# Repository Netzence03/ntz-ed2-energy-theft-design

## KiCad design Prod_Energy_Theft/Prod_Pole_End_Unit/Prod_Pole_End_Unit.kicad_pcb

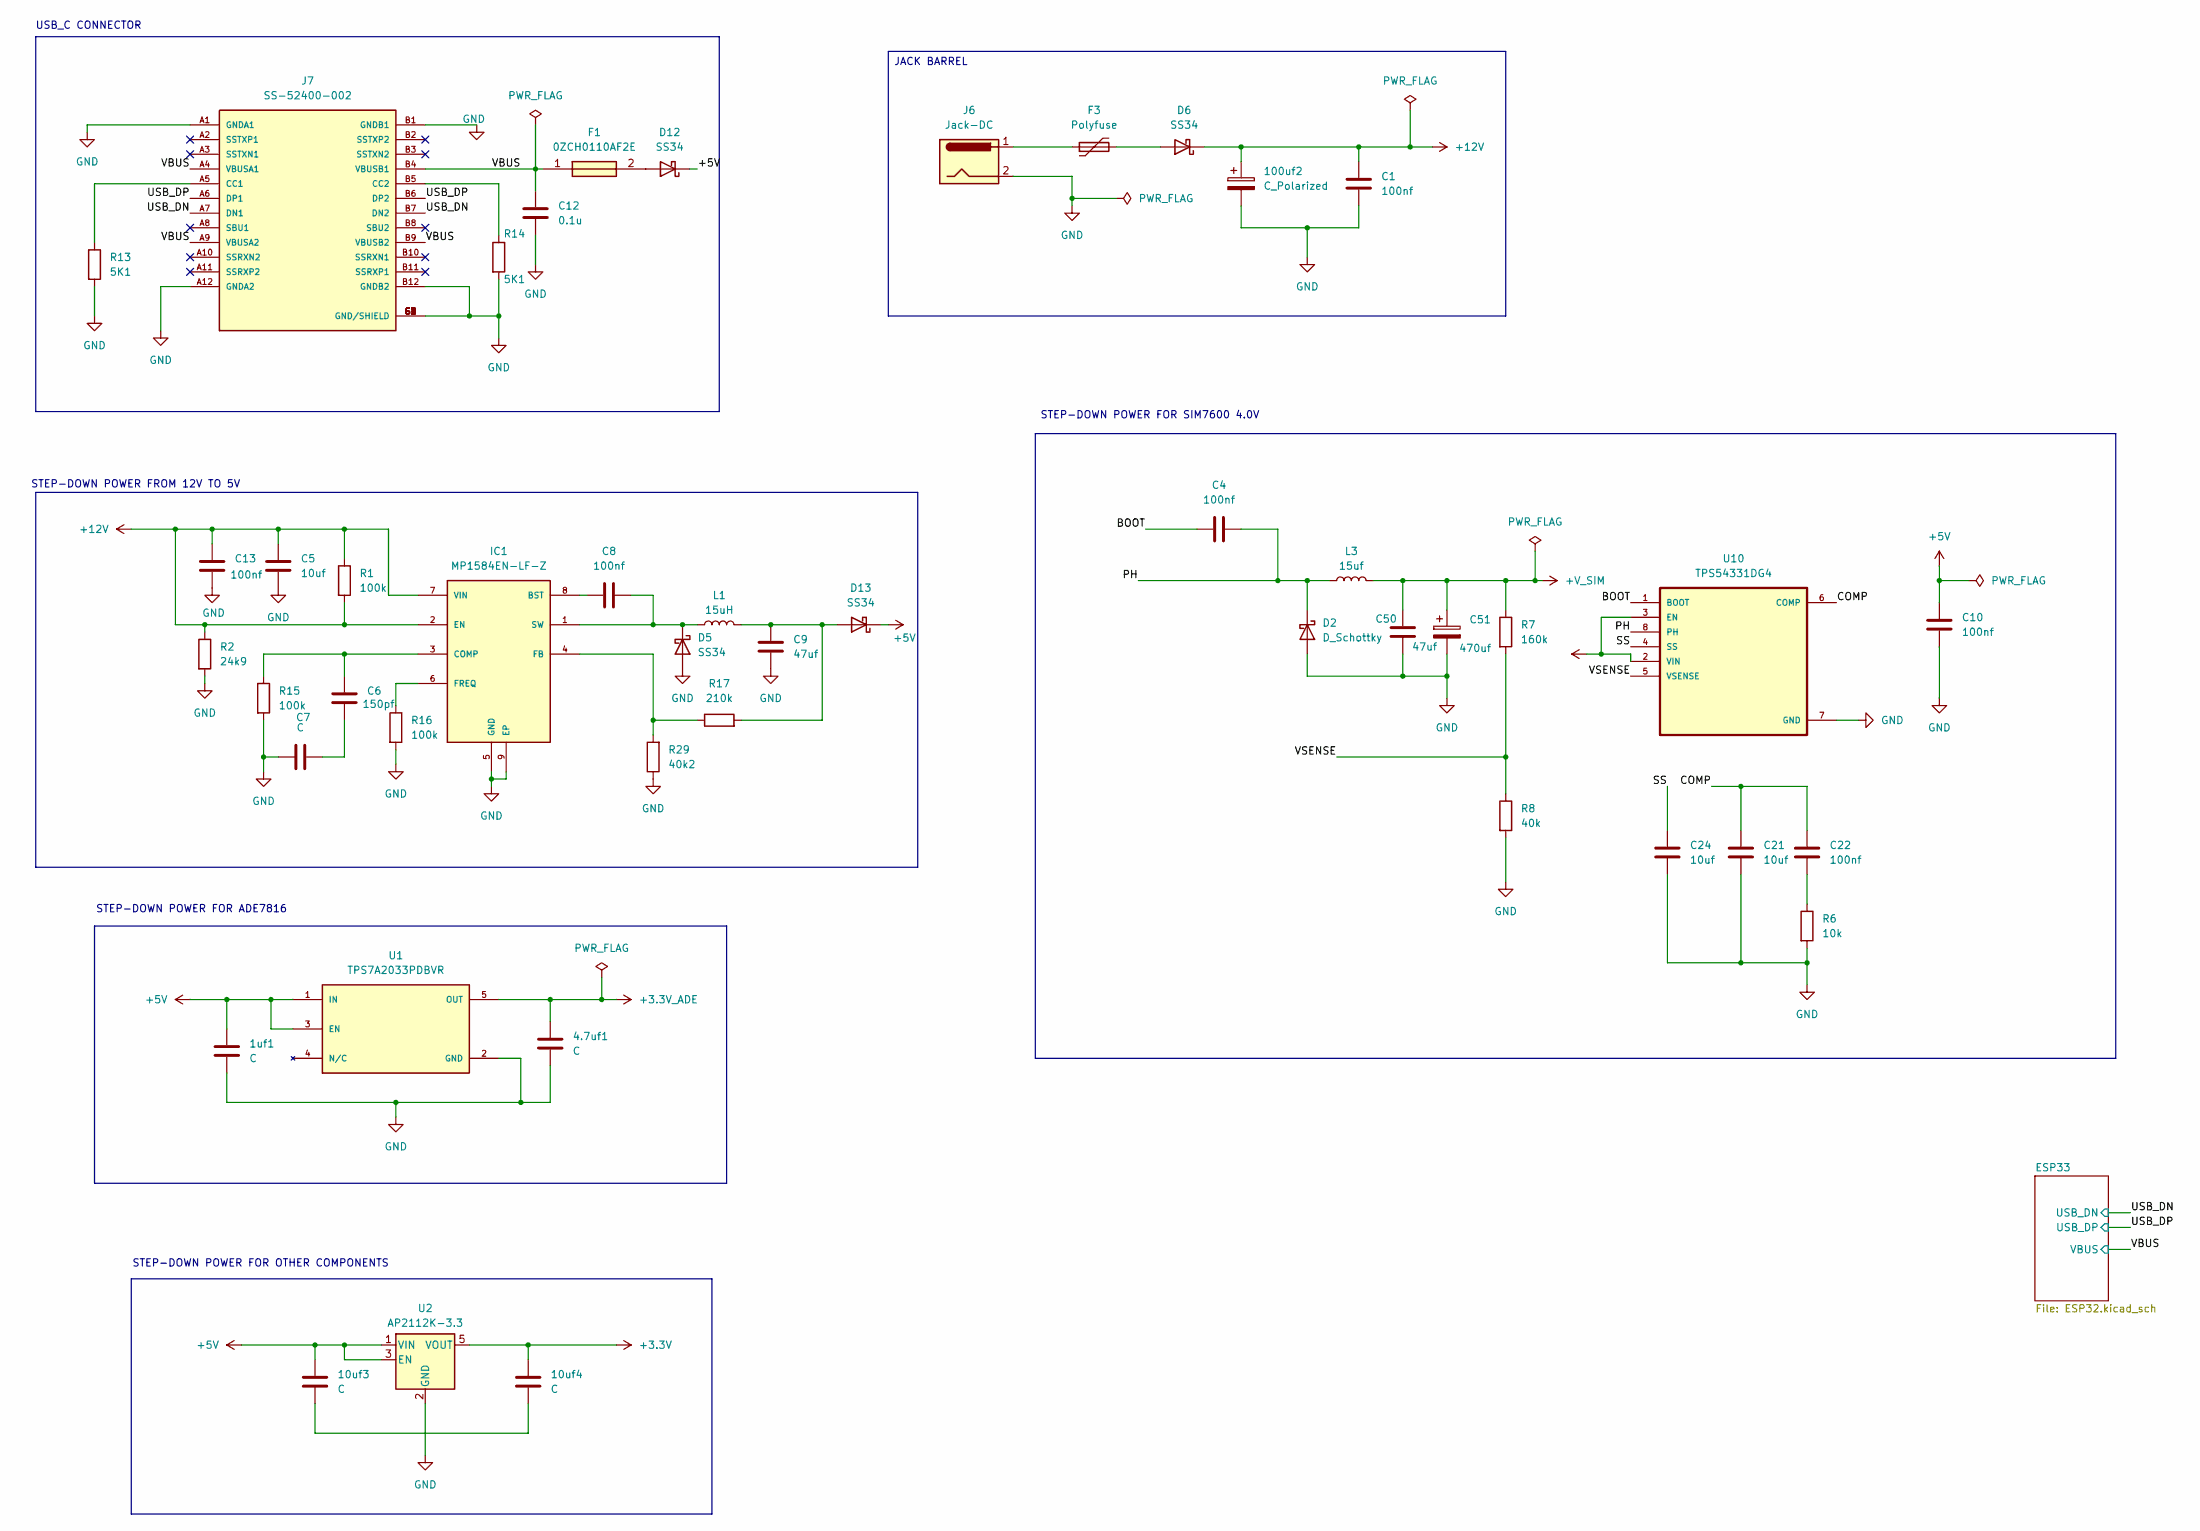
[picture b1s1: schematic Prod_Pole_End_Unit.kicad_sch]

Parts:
1uf1, 4.7uf1, 10uf3, 10uf4: C; C_0805_2012Metric
100uf2: C_Polarized; C_0805_2012Metric
C1, C4, C8, C10, C13, C22: 100nf; C_0805_2012Metric
C5, C21, C24: 10uf; C_0805_2012Metric
C6: 150pf; C_0805_2012Metric
C7: C; C_0805_2012Metric
C9: 47uf; C_0805_2012Metric; Voltage 16V; MPN GRM32ER71C476KE15
C12: 0.1u; C_0805_2012Metric
C50: 47uf; C_0805_2012Metric
C51: 470uf; C_0805_2012Metric
D2: D_Schottky; D_SMA
D5, D6, D12, D13: SS34; D_SMA
F1: 0ZCH0110AF2E; FUSC3226X100N; Manufacturer_Part_Number 0ZCH0110AF2E
F3: Polyfuse; Fuse_1206_3216Metric
IC1: MP1584EN-LF-Z; SOIC127P600X170-9N; MOUSER_PART_NUMBER 946-MP1584ENLFZ
J6: Jack-DC; BarrelJack_GCT_DCJ200-10-A_Horizontal
J7: SS-52400-002; BELFUSE_SS-52400-002; PARTREV A0
L1: 15uH; L_0805_2012Metric
L3: 15uf; L_0805_2012Metric
R1, R15, R16: 100k; R_0805_2012Metric
R2: 24k9; R_0805_2012Metric
R6: 10k; R_0805_2012Metric
R7: 160k; R_0805_2012Metric
R8: 40k; R_0805_2012Metric
R13, R14: 5K1; R_0805_2012Metric
R17: 210k; R_0805_2012Metric
R29: 40k2; R_0805_2012Metric
U1: TPS7A2033PDBVR; SOT95P280X145-5N; PARTREV H
U2: AP2112K-3.3; SOT-23-5
U10: TPS54331DG4; SOIC127P599X175-8N

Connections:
+3.3V: 10uf4.1, U2.5 (VOUT); also elsewhere on the board
+3.3V_ADE: 4.7uf1.1, U1.5 (OUT); also elsewhere on the board
+5V: 1uf1.1, 10uf3.1, C10.1, D12.1 (K), D13.1 (K), U1.1 (IN), U1.3 (EN), U2.1 (VIN), U2.3 (EN), U10.2 (VIN), U10.3 (EN)
+12V: 100uf2.1, C1.1, C5.1, C13.1, D6.1 (K), IC1.2 (EN), IC1.7 (VIN), R1.1, R1.2, R2.1
+V_SIM: C50.1, C51.1, L3.2, R7.1; also elsewhere on the board
/BOOT: C4.1, U10.1 (BOOT)
/COMP: C21.1, C22.1, U10.6 (COMP)
/PH: C4.2, D2.1 (K), L3.1, U10.8 (PH)
/SS: C24.1, U10.4 (SS)
/USB_DN: J7.A7 (DN1), J7.B7 (DN2); also elsewhere on the board
/USB_DP: J7.A6 (DP1), J7.B6 (DP2); also elsewhere on the board
/VBUS: C12.1, F1.1, J7.A4 (VBUSA1), J7.A9 (VBUSA2), J7.B4 (VBUSB1), J7.B9 (VBUSB2); also elsewhere on the board
/VSENSE: R7.2, R8.1, U10.5 (VSENSE)
GND: 1uf1.2, 4.7uf1.2, 100uf2.2, C1.2, C5.2, C7.1, C9.2, C10.2, C12.2, C13.2, C21.2, C24.2, C50.2, C51.2, D2.2 (A), D5.2 (A), IC1.5 (GND), IC1.9 (EP), J6.2, J7.A1 (GNDA1), J7.A12 (GNDA2), J7.B1 (GNDB1), J7.B12 (GNDB2), J7.G1 (GND/SHIELD), J7.G2 (GND/SHIELD), J7.G3 (GND/SHIELD), J7.G4 (GND/SHIELD), J7.S1 (GND/SHIELD), J7.S2 (GND/SHIELD), J7.S3 (GND/SHIELD), J7.S4 (GND/SHIELD), R2.2, R6.2, R8.2, R13.2, R14.2, R15.2, R16.2, R29.1, U1.2 (GND), U2.2 (GND), U10.7 (GND); also elsewhere on the board
unnamed: 10uf3.2, 10uf4.2
unnamed: C6.2, C7.2
unnamed: C22.2, R6.1
unnamed: C8.2, D5.1 (K), IC1.1 (SW), L1.1
unnamed: D6.2 (A), F3.2
unnamed: D12.2 (A), F1.2
unnamed: C9.1, D13.2 (A), L1.2, R17.2
unnamed: F3.1, J6.1
unnamed: C8.1, IC1.8 (BST)
unnamed: C6.1, IC1.3 (COMP), R15.1
unnamed: IC1.4 (FB), R17.1, R29.2
unnamed: IC1.6 (FREQ), R16.1
unnamed: J7.A5 (CC1), R13.1
unnamed: J7.B5 (CC2), R14.1

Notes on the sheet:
STEP-DOWN POWER FROM 12V TO 5V
STEP-DOWN POWER FOR ADE7816
STEP-DOWN POWER FOR SIM7600 4.0V
STEP-DOWN POWER FOR OTHER COMPONENTS
USB_C CONNECTOR
JACK BARREL

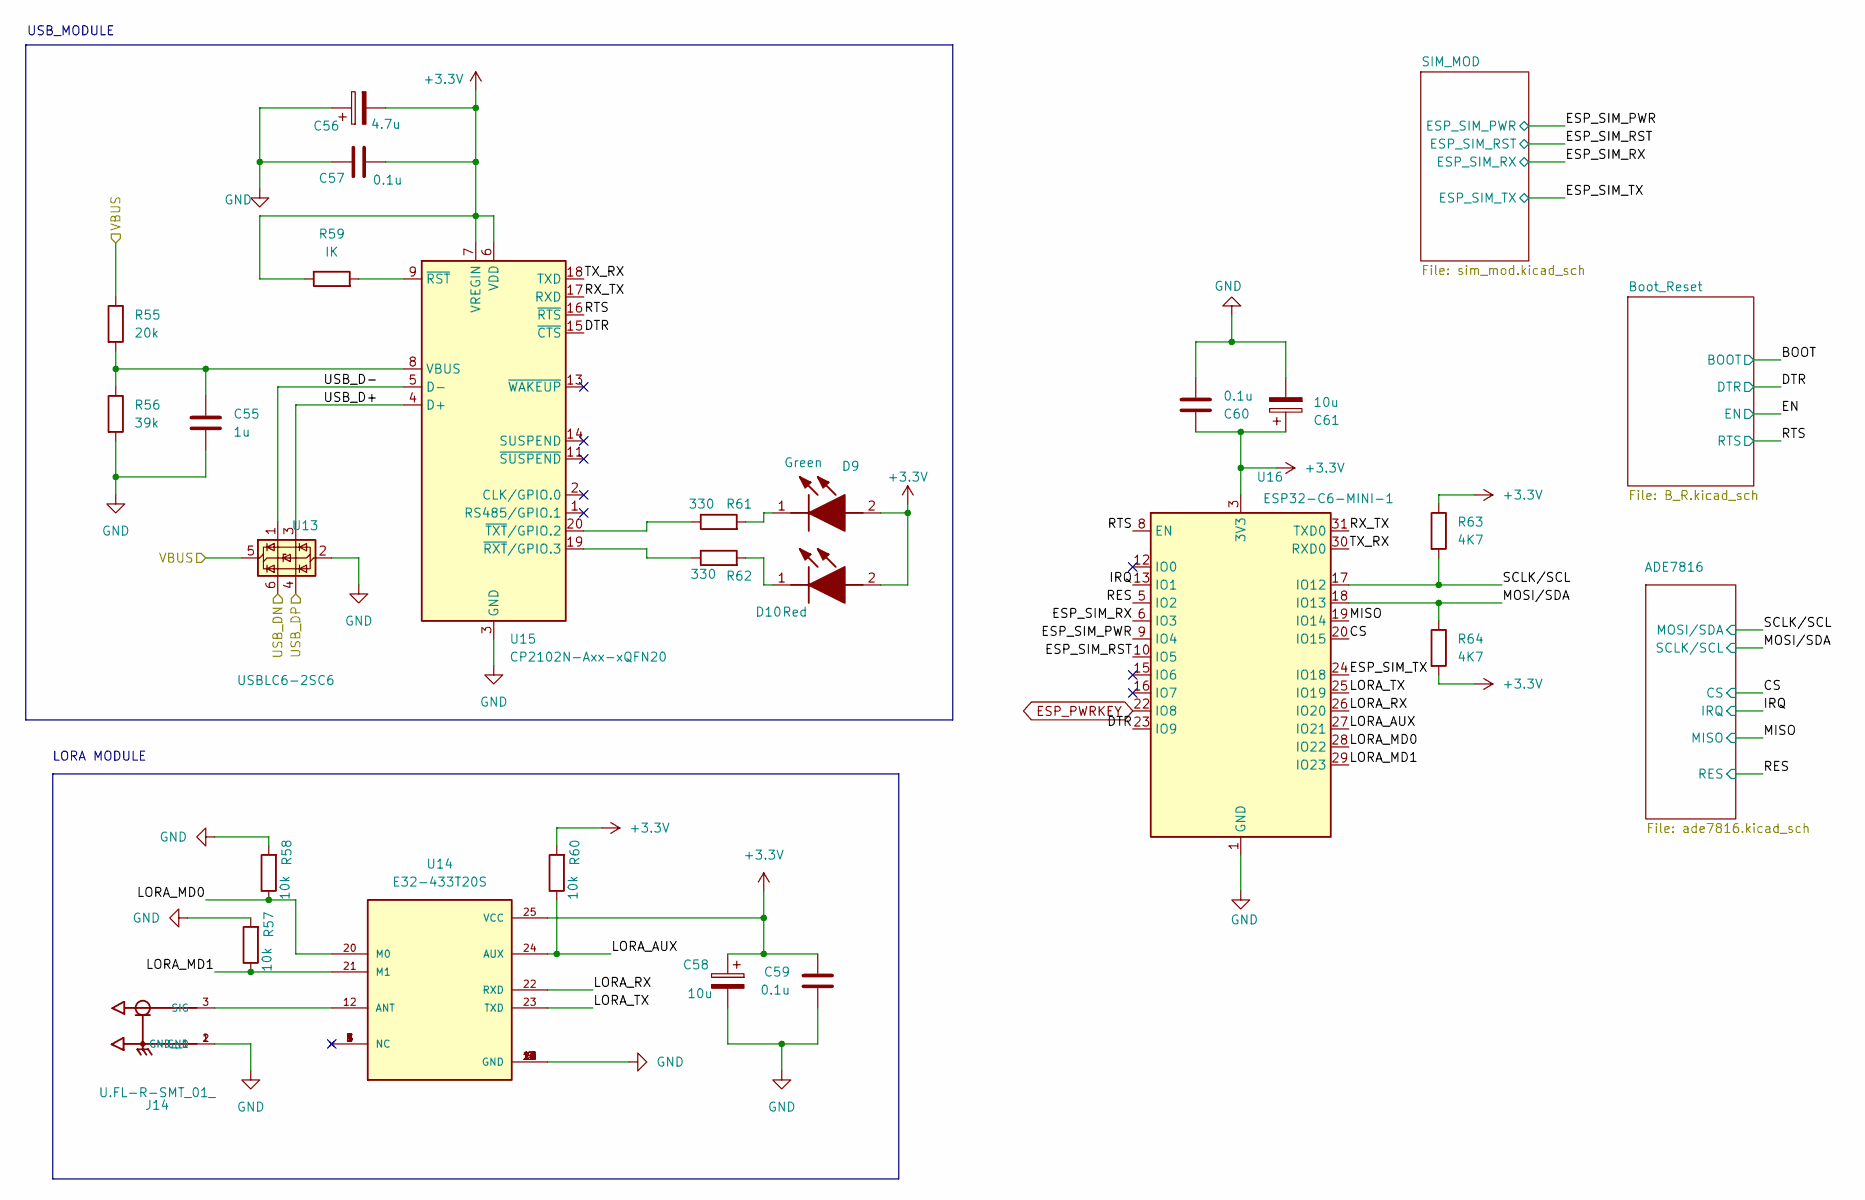
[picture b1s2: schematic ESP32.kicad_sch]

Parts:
C55: 1u; C_0805_2012Metric
C56: 4.7u; C_0805_2012Metric
C57, C59, C60: 0.1u; C_0805_2012Metric
C58, C61: 10u; C_0805_2012Metric
D9: Green; LEDC2012X120N; Manufacturer_Part_Number LTST-C170GKT; Mouser Part Number 859-LTST-C170GKT
D10: Red; LEDC2012X120N; Manufacturer_Part_Number LTST-C170KRKT; Mouser Part Number 859-LTST-C170KRKT
J14: U.FL-R-SMT_01_; HRS_U.FL-R-SMT_01_
R55: 20k; R_0805_2012Metric
R56: 39k; R_0805_2012Metric
R57, R58, R60: 10k; R_0805_2012Metric
R59: IK; R_0805_2012Metric
R61, R62: 330; R_0805_2012Metric
R63, R64: 4K7; R_0805_2012Metric
U13: USBLC6-2SC6; SOT-23-6
U14: E32-433T20S; MODULE_E32-433T20S; PARTREV 1.00
U15: CP2102N-Axx-xQFN20; IC_CP2102N-A01-GQFN20
U16: ESP32-C6-MINI-1

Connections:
+3.3V: C56.2, C57.2, C58.1, C59.1, C60.1, C61.1, D9.2 (A), D10.2 (A), R59.1, R60.2, R63.1, R64.2, U14.25 (VCC), U15.6 (VDD), U15.7 (VREGIN), U16.3 (3V3); also elsewhere on the board
/ESP33/CS: U16.20 (IO15); also elsewhere on the board
/ESP33/DTR: U15.15 (~CTS), U16.23 (IO9); also elsewhere on the board
/ESP33/ESP_SIM_PWR: U16.9 (IO4); also elsewhere on the board
/ESP33/ESP_SIM_RST: U16.10 (IO5); also elsewhere on the board
/ESP33/ESP_SIM_RX: U16.6 (IO3); also elsewhere on the board
/ESP33/ESP_SIM_TX: U16.24 (IO18); also elsewhere on the board
/ESP33/IRQ: U16.13 (IO1); also elsewhere on the board
/ESP33/LORA_AUX: R60.1, U14.24 (AUX), U16.27 (IO21)
/ESP33/LORA_MD0: R58.1, U14.20 (M0), U16.28 (IO22)
/ESP33/LORA_MD1: R57.1, U14.21 (M1), U16.29 (IO23)
/ESP33/LORA_RX: U14.22 (RXD), U16.26 (IO20)
/ESP33/LORA_TX: U14.23 (TXD), U16.25 (IO19)
/ESP33/MISO: U16.19 (IO14); also elsewhere on the board
/ESP33/MOSI/SDA: R64.1, U16.18 (IO13); also elsewhere on the board
/ESP33/RES: U16.5 (IO2); also elsewhere on the board
/ESP33/RTS: U15.16 (~RTS), U16.8 (EN); also elsewhere on the board
/ESP33/RX_TX: U15.17 (RXD), U16.31 (TXD0)
/ESP33/SCLK/SCL: R63.2, U16.17 (IO12); also elsewhere on the board
/ESP33/TX_RX: U15.18 (TXD), U16.30 (RXD0)
/ESP33/USB_D+: U13.3 (I/O2), U15.4 (D+)
/ESP33/USB_D-: U13.1 (I/O1), U15.5 (D-)
/USB_DN: U13.6 (I/O1); also elsewhere on the board
/USB_DP: U13.4 (I/O2); also elsewhere on the board
/VBUS: R55.1, U13.5 (VBUS); also elsewhere on the board
ESP_PWRKEY: U16.22 (IO8); also elsewhere on the board
GND: C55.2, C56.1, C57.1, C58.2, C59.2, C60.2, C61.2, J14.1 (GND), J14.2 (GND__1), R56.2, R57.2, R58.2, U13.2 (GND), U14.2 (GND), U14.8 (GND), U14.11 (GND), U14.13 (GND), U14.14 (GND), U14.15 (GND), U14.16 (GND), U14.19 (GND), U14.26 (GND), U15.3 (GND), U15.12 (GND), U15.21 (GND), U16.1 (GND), U16.2 (GND), U16.11 (GND), U16.14 (GND), U16.36 (GND), U16.37 (GND), U16.38 (GND), U16.39 (GND), U16.40 (GND), U16.41 (GND), U16.42 (GND), U16.43 (GND), U16.44 (GND), U16.45 (GND), U16.46 (GND), U16.47 (GND), U16.48 (GND), U16.49 (GND), U16.50 (GND), U16.51 (GND), U16.52 (GND), U16.53 (GND); also elsewhere on the board
unnamed: D9.1 (K), R61.2
unnamed: D10.1 (K), R62.2
unnamed: J14.3 (SIG), U14.12 (ANT)
unnamed: C55.1, R55.2, R56.1, U15.8 (VBUS)
unnamed: R59.2, U15.9 (~RST)
unnamed: R62.1, U15.19 (~RXT/GPIO.3)
unnamed: R61.1, U15.20 (~TXT/GPIO.2)

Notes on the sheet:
LORA MODULE
USB_MODULE

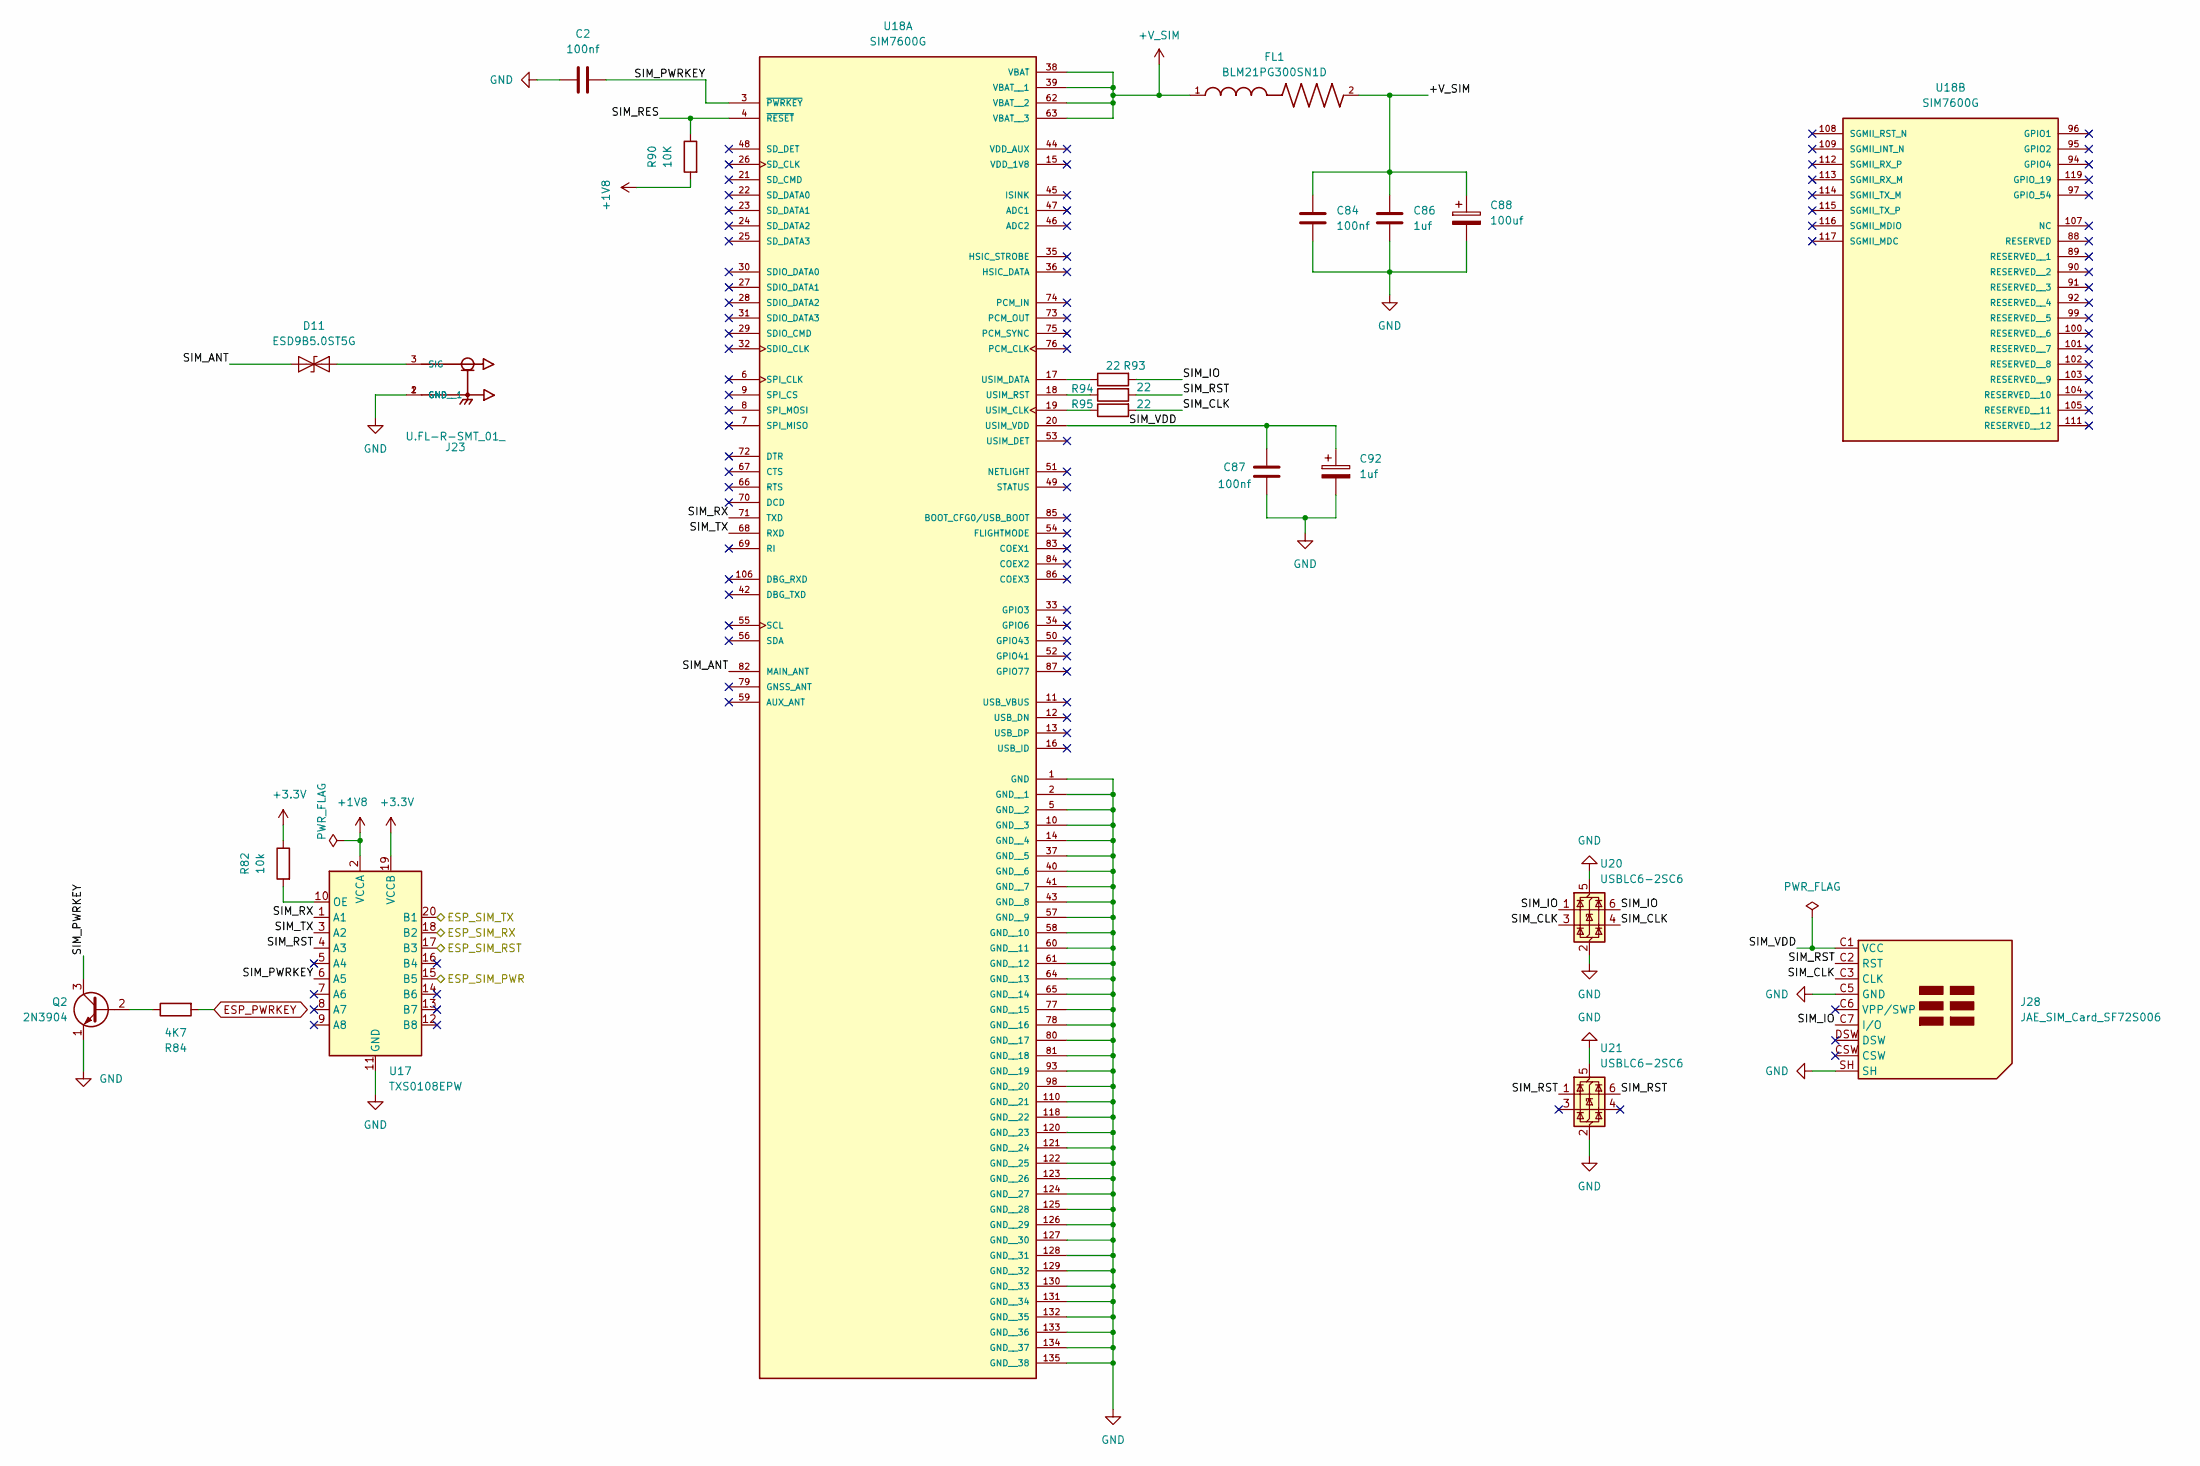
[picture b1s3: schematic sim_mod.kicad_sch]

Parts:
C2, C84, C87: 100nf; C_0805_2012Metric
C86, C92: 1uf; C_0805_2012Metric
C88: 100uf; C_0805_2012Metric
D11: ESD9B5.0ST5G; D_SOD-923
FL1: BLM21PG300SN1D; BEADC2012X105N
J23: U.FL-R-SMT_01_; HRS_U.FL-R-SMT_01_
J28: JAE_SIM_Card_SF72S006
Q2: 2N3904; TO-92_Inline
R82: 10k; R_0805_2012Metric
R84: 4K7; R_0805_2012Metric
R90: 10K; R_0805_2012Metric
R93, R94, R95: 22; R_0805_2012Metric
U17: TXS0108EPW; TSSOP-20_4.4x6.5mm_P0.65mm
U18: SIM7600G; IC_SIM7600G
U20, U21: USBLC6-2SC6; SOT-23-6

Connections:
+1V8: R90.2, U17.2 (VCCA)
+3.3V: R82.1, U17.19 (VCCB); also elsewhere on the board
+V_SIM: C84.1, C86.1, C88.1, FL1.1, FL1.2, U18.38 (VBAT), U18.39 (VBAT__1), U18.62 (VBAT__2), U18.63 (VBAT__3); also elsewhere on the board
/ESP33/ESP_SIM_PWR: U17.15 (B5); also elsewhere on the board
/ESP33/ESP_SIM_RST: U17.17 (B3); also elsewhere on the board
/ESP33/ESP_SIM_RX: U17.18 (B2); also elsewhere on the board
/ESP33/ESP_SIM_TX: U17.20 (B1); also elsewhere on the board
/ESP33/SIM_MOD/SIM_ANT: D11.1 (A1), U18.82 (MAIN_ANT)
/ESP33/SIM_MOD/SIM_CLK: J28.C3 (CLK), R95.2, U20.3 (I/O2), U20.4 (I/O2)
/ESP33/SIM_MOD/SIM_IO: J28.C7 (I/O), R93.2, U20.1 (I/O1), U20.6 (I/O1)
/ESP33/SIM_MOD/SIM_PWRKEY: C2.2, Q2.3 (C), U17.6 (A5), U18.3 (~PWRKEY)
/ESP33/SIM_MOD/SIM_RES: R90.1, U18.4 (~RESET)
/ESP33/SIM_MOD/SIM_RST: J28.C2 (RST), R94.2, U17.4 (A3), U21.1 (I/O1), U21.6 (I/O1)
/ESP33/SIM_MOD/SIM_RX: U17.1 (A1), U18.71 (TXD)
/ESP33/SIM_MOD/SIM_TX: U17.3 (A2), U18.68 (RXD)
/ESP33/SIM_MOD/SIM_VDD: C87.1, C92.1, J28.C1 (VCC), U18.20 (USIM_VDD)
ESP_PWRKEY: R84.2; also elsewhere on the board
GND: C2.1, C84.2, C86.2, C87.2, C88.2, C92.2, J23.1 (GND), J23.2 (GND__1), J28.C5 (GND), J28.SH, Q2.1 (E), U17.11 (GND), U18.1 (GND), U18.2 (GND__1), U18.5 (GND__2), U18.10 (GND__3), U18.14 (GND__4), U18.37 (GND__5), U18.40 (GND__6), U18.41 (GND__7), U18.43 (GND__8), U18.57 (GND__9), U18.58 (GND__10), U18.60 (GND__11), U18.61 (GND__12), U18.64 (GND__13), U18.65 (GND__14), U18.77 (GND__15), U18.78 (GND__16), U18.80 (GND__17), U18.81 (GND__18), U18.93 (GND__19), U18.98 (GND__20), U18.110 (GND__21), U18.118 (GND__22), U18.120 (GND__23), U18.121 (GND__24), U18.122 (GND__25), U18.123 (GND__26), U18.124 (GND__27), U18.125 (GND__28), U18.126 (GND__29), U18.127 (GND__30), U18.128 (GND__31), U18.129 (GND__32), U18.130 (GND__33), U18.131 (GND__34), U18.132 (GND__35), U18.133 (GND__36), U18.134 (GND__37), U18.135 (GND__38), U20.2 (GND), U20.5 (VBUS), U21.2 (GND), U21.5 (VBUS); also elsewhere on the board
unnamed: D11.2 (A2), J23.3 (SIG)
unnamed: Q2.2 (B), R84.1
unnamed: R82.2, U17.10 (OE)
unnamed: R95.1, U18.19 (USIM_CLK)
unnamed: R93.1, U18.17 (USIM_DATA)
unnamed: R94.1, U18.18 (USIM_RST)

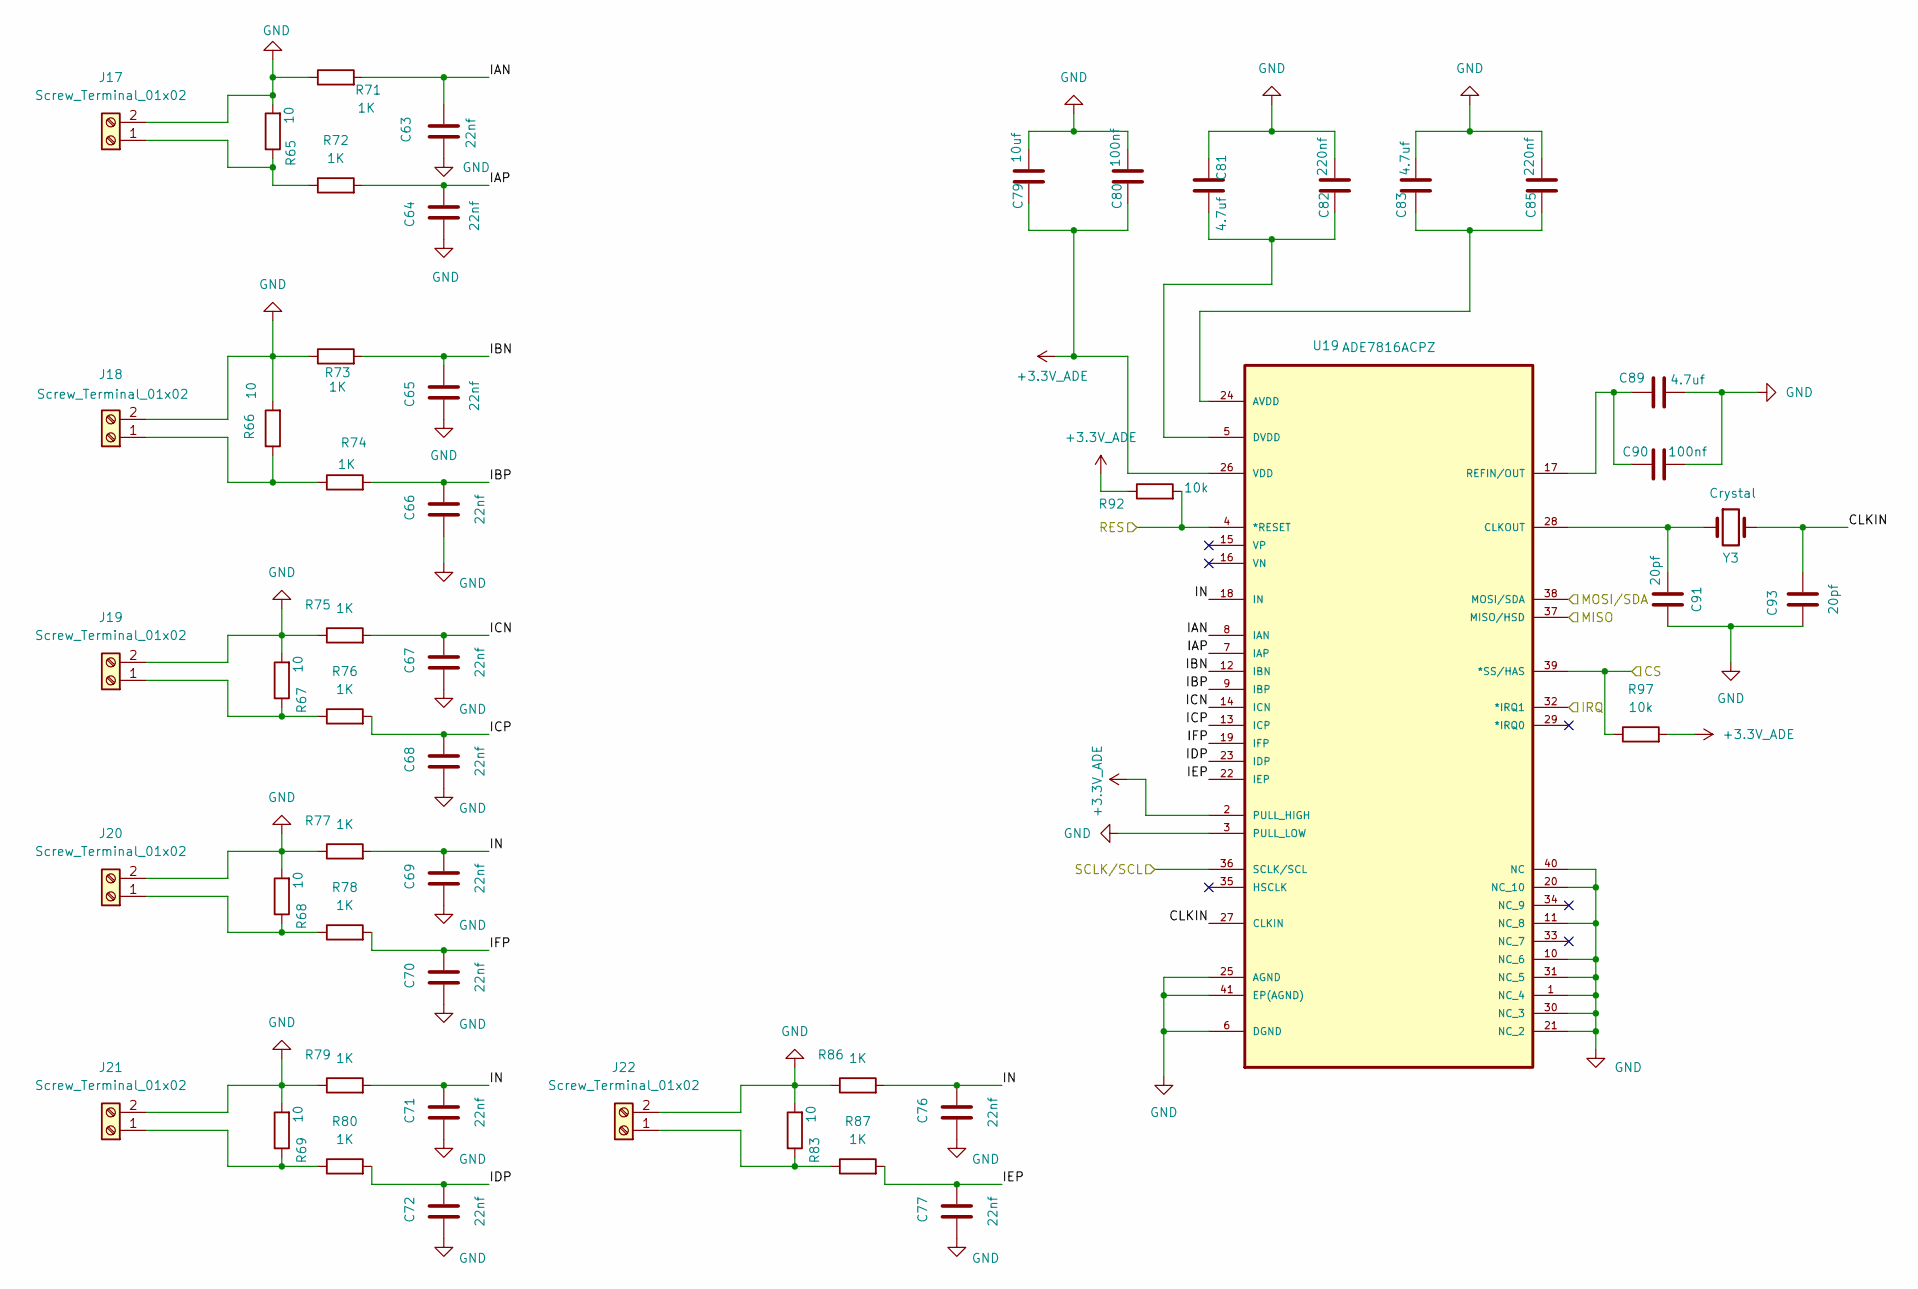
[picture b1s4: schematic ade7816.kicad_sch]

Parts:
C63, C64, C65, C66, C67, C68, C69, C70, C71, C72, C76, C77: 22nf; C_0805_2012Metric
C79: 10uf; C_0805_2012Metric
C80, C90: 100nf; C_0805_2012Metric
C81, C83, C89: 4.7uf; C_0805_2012Metric
C82, C85: 220nf; C_0805_2012Metric
C91, C93: 20pf; C_0805_2012Metric
J17, J18, J19, J20, J21, J22: Screw_Terminal_01x02; TerminalBlock_Phoenix_MKDS-1,5-2-5.08_1x02_P5.08mm_Horizont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
R65, R66, R67, R68, R69, R83: 10; R_0805_2012Metric
R71, R72, R73, R74, R75, R76, R77, R78, R79, R80, R86, R87: 1K; R_0805_2012Metric
R92, R97: 10k; R_0805_2012Metric
U19: ADE7816ACPZ; QFN50P600X600X80-41N; MPN ADE7816ACPZ
Y3: Crystal; Crystal_SMD_3225-4Pin_3.2x2.5mm

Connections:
+3.3V_ADE: C79.1, C80.1, R92.1, R97.2, U19.2 (PULL_HIGH), U19.26 (VDD); also elsewhere on the board
/ESP33/ADE7816/CLKIN: C93.2, U19.27 (CLKIN), Y3.2
/ESP33/ADE7816/IAN: C63.2, R71.2, U19.8 (IAN)
/ESP33/ADE7816/IAP: C64.2, R72.2, U19.7 (IAP)
/ESP33/ADE7816/IBN: C65.2, R73.2, U19.12 (IBN)
/ESP33/ADE7816/IBP: C66.2, R74.2, U19.9 (IBP)
/ESP33/ADE7816/ICN: C67.2, R75.2, U19.14 (ICN)
/ESP33/ADE7816/ICP: C68.2, R76.2, U19.13 (ICP)
/ESP33/ADE7816/IDP: C72.2, R80.2, U19.23 (IDP)
/ESP33/ADE7816/IEP: C77.2, R87.2, U19.22 (IEP)
/ESP33/ADE7816/IFP: C70.2, R78.2, U19.19 (IFP)
/ESP33/ADE7816/IN: C69.2, C71.2, C76.2, R77.2, R79.2, R86.2, U19.18 (IN)
/ESP33/CS: R97.1, U19.39 (*SS/HAS); also elsewhere on the board
/ESP33/IRQ: U19.32 (*IRQ1); also elsewhere on the board
/ESP33/MISO: U19.37 (MISO/HSD); also elsewhere on the board
/ESP33/MOSI/SDA: U19.36 (SCLK/SCL); also elsewhere on the board
/ESP33/RES: R92.2, U19.4 (*RESET); also elsewhere on the board
/ESP33/SCLK/SCL: U19.38 (MOSI/SDA); also elsewhere on the board
GND: C63.1, C64.1, C65.1, C66.1, C67.1, C68.1, C69.1, C70.1, C71.1, C72.1, C76.1, C77.1, C79.2, C80.2, C81.1, C82.2, C83.2, C85.2, C89.2, C90.2, C91.1, C93.1, J17.2, J18.2, J19.2, J20.2, J21.2, J22.2, R65.2, R66.2, R67.2, R68.2, R69.2, R71.1, R73.1, R75.1, R77.1, R79.1, R83.2, R86.1, U19.1 (NC_4), U19.3 (PULL_LOW), U19.6 (DGND), U19.10 (NC_6), U19.11 (NC_8), U19.20 (NC_10), U19.21 (NC_2), U19.25 (AGND), U19.30 (NC_3), U19.31 (NC_5), U19.40 (NC), U19.41 (EP(AGND)); also elsewhere on the board
unnamed: J17.1, R65.1, R72.1
unnamed: J18.1, R66.1, R74.1
unnamed: J19.1, R67.1, R76.1
unnamed: J20.1, R68.1, R78.1
unnamed: J21.1, R69.1, R80.1
unnamed: J22.1, R83.1, R87.1
unnamed: C83.1, C85.1, U19.24 (AVDD)
unnamed: C91.2, U19.28 (CLKOUT), Y3.1
unnamed: C81.2, C82.1, U19.5 (DVDD)
unnamed: C89.1, C90.1, U19.17 (REFIN/OUT)

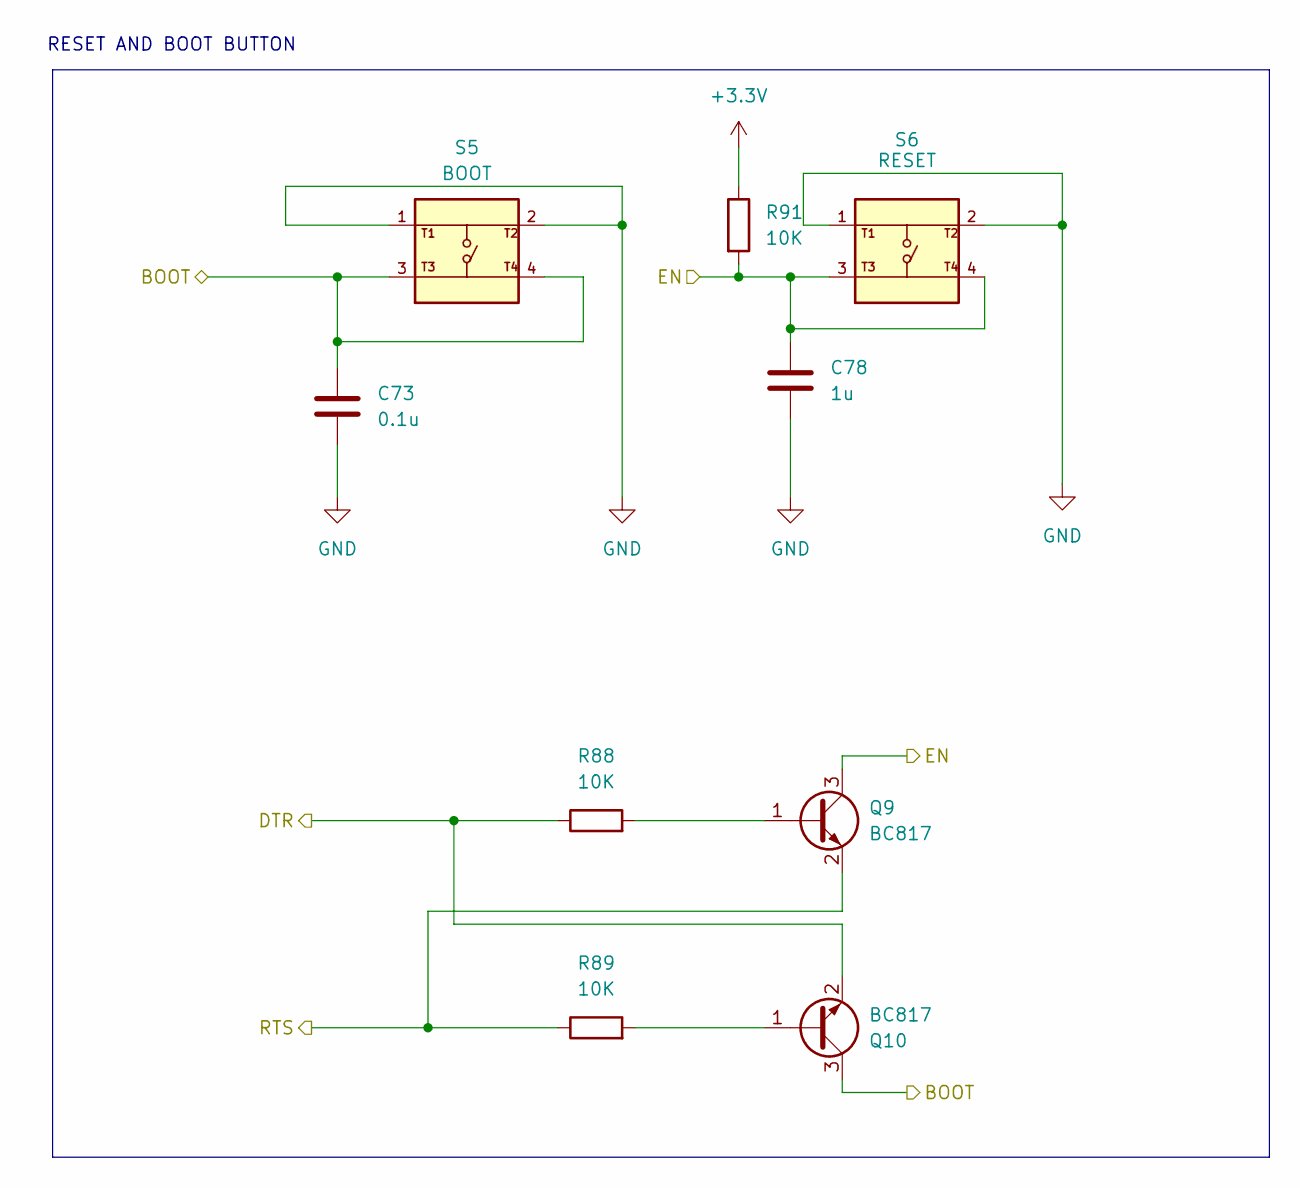
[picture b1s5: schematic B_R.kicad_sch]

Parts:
C73: 0.1u; C_0805_2012Metric
C78: 1u; C_0805_2012Metric
Q9, Q10: BC817; SOT-23
R88, R89, R91: 10K; R_0805_2012Metric
S5: BOOT; SW_USLPT2819DT2TR; PARTREV P
S6: RESET; SW_USLPT2819DT2TR; PARTREV P

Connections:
+3.3V: R91.1; also elsewhere on the board
/ESP33/BOOT: C73.1, Q10.3 (C), S5.3, S5.4
/ESP33/DTR: Q10.2 (E), R88.1; also elsewhere on the board
/ESP33/EN: C78.1, Q9.3 (C), R91.2, S6.3, S6.4
/ESP33/RTS: Q9.2 (E), R89.1; also elsewhere on the board
GND: C73.2, C78.2, S5.1, S5.2, S6.1, S6.2; also elsewhere on the board
unnamed: Q9.1 (B), R88.2
unnamed: Q10.1 (B), R89.2

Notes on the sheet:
RESET AND BOOT BUTTON

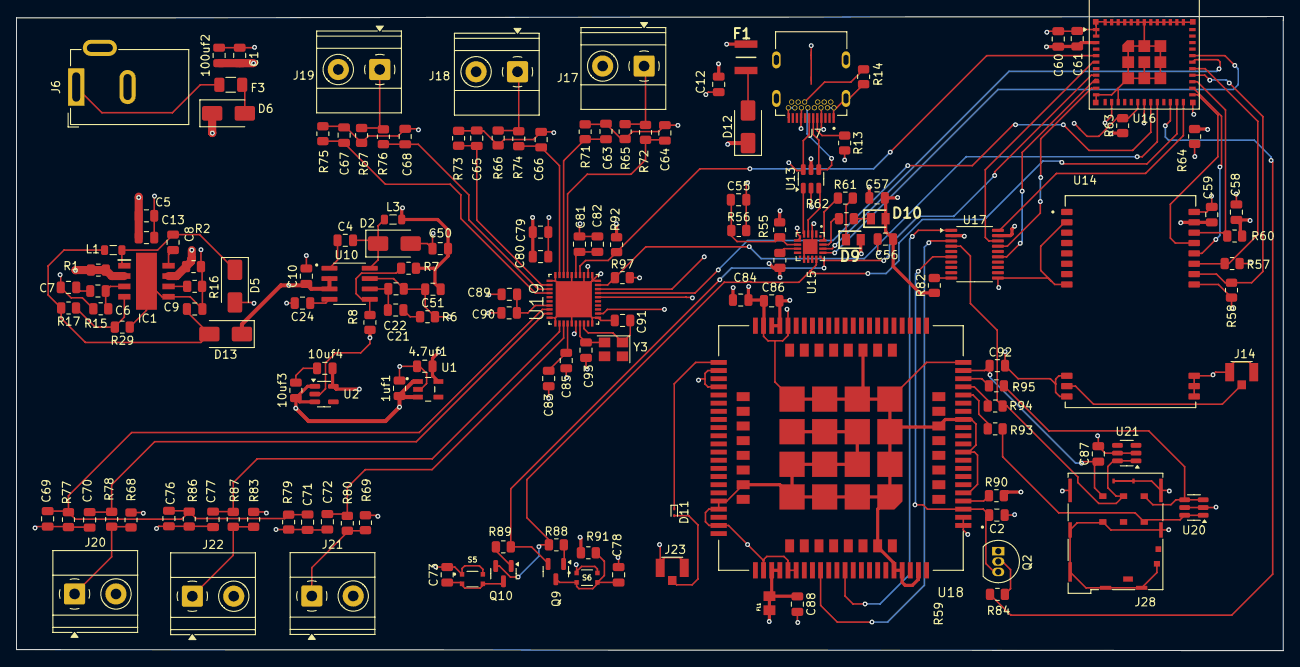
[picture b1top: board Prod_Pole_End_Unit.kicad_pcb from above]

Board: 4 copper layers, 155.4 x 77.8 mm, 150 parts (0 on the bottom side), 98 nets.
